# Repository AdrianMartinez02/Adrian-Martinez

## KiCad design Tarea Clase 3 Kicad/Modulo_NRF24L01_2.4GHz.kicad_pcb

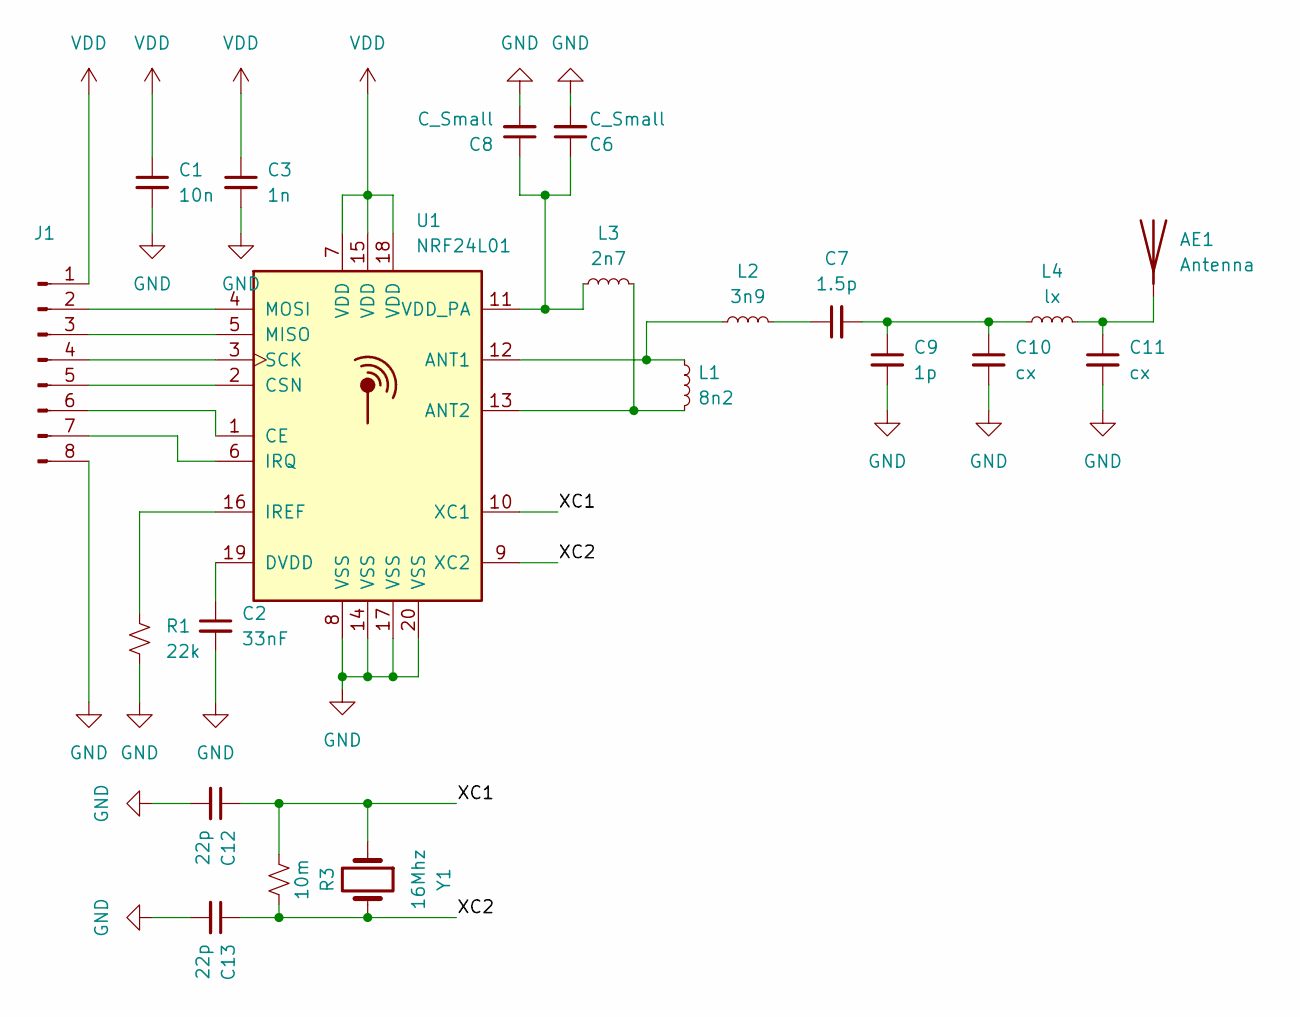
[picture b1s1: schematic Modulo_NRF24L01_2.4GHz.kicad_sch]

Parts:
AE1: Antenna; Texas_SWRA117D_2.4GHz_Right
C1: 10n; C_0603_1608Metric
C2: 33nF; C_0603_1608Metric
C3: 1n; C_0603_1608Metric
C6, C8: C_Small; C_0603_1608Metric
C7: 1.5p; C_0603_1608Metric
C9: 1p; C_0603_1608Metric
C10, C11: cx; C_0603_1608Metric
C12, C13: 22p; C_0603_1608Metric
J1: Conn_01x08_Pin; Hirose_DF13-08P-1.25DSA_1x08_P1.25mm_Vertical
L1: 8n2; L_0603_1608Metric
L2: 3n9; L_0603_1608Metric
L3: 2n7; L_0603_1608Metric
L4: lx; L_0603_1608Metric
R1: 22k; R_0201_0603Metric
R3: 10m; R_0201_0603Metric
U1: NRF24L01; QFN-20-1EP_4x4mm_P0.5mm_EP2.5x2.5mm
Y1: 16Mhz; Crystal_SMD_3215-2Pin_3.2x1.5mm

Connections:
/XC1: C12.1, R3.2, U1.10 (XC1), Y1.1
/XC2: C13.1, R3.1, U1.9 (XC2), Y1.2
GND: C1.2, C2.2, C3.2, C6.2, C8.2, C9.2, C10.2, C11.2, C12.2, C13.2, J1.8, R1.2, U1.8 (VSS), U1.14 (VSS), U1.17 (VSS), U1.20 (VSS)
unnamed: AE1.1 (A), C11.1, L4.2
unnamed: C7.1, L2.2
unnamed: C7.2, C9.1, C10.1, L4.1
unnamed: J1.2, U1.4 (MOSI)
unnamed: J1.3, U1.5 (MISO)
unnamed: J1.4, U1.3 (SCK)
unnamed: J1.5, U1.2 (CSN)
unnamed: J1.6, U1.1 (CE)
unnamed: J1.7, U1.6 (IRQ)
unnamed: L1.1, L2.1, U1.12 (ANT1)
unnamed: L1.2, L3.2, U1.13 (ANT2)
unnamed: C2.1, U1.19 (DVDD)
unnamed: R1.1, U1.16 (IREF)
unnamed: C6.1, C8.1, L3.1, U1.11 (VDD_PA)
VDD: C1.1, C3.1, J1.1, U1.7 (VDD), U1.15 (VDD), U1.18 (VDD)

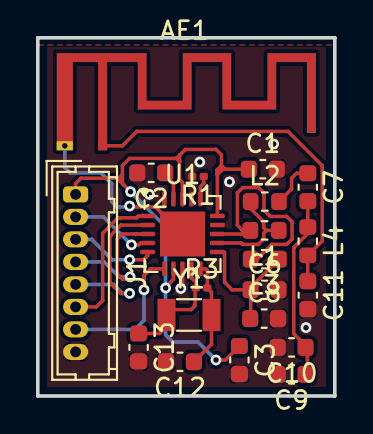
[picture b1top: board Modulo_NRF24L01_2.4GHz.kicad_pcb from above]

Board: 2 copper layers, 16.5 x 19.9 mm, 21 parts (0 on the bottom side), 18 nets.
